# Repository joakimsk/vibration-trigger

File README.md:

# Vibration activated trigger / LED

We use a Piezoelectric element with an operational amplifier (low power amplifier, LM386) to detect small movements. Sensitivity is controlled with potentiometer RV1.

A monostable 555-timer gets triggered, and can be continuously reset, to maintain stable output signal.

The output signal is in this case, driving a LED, but could be used to activate external devices, for example, the purpose of which this was made, an off-the-shelf GPS tracker.

Power supply should probably be 5v regulated... So consider using LM7805 or alternatives. I think a USB power supply connected to a 12v unregulated lead battery should be ok, 5-5.4 volts.

Schematic as PDF available [here](./renders/full_circuit.pdf)

Circuit consists of three components, which I try to explain here.

Latest revision 1.0.0 (first complete prototype).

## Mounting and physical information
Top plane is VCC (+5v), bottom plane is GND.

Mounting is supposed to be with 2x 3mm screw, 1x 2mm screw, 1x 1mm screw (just to test hole sizes).

Full PCB dimensions should be 43.18mm x 40.64mm.

The piezoelectric element needs to be well secured to the vibrating thing, be it your boat engine, your plane or your car. It can very well be a piezoelectric speaker.

## Component: Trigger
The high voltage generated when a piezoelectric crystal is exposed to mechanical load, is compared using LM386 low power amplifier (Voltage Comparator configuration), to an adjustable reference voltage up to VCC (+5v).

I think I ended up with using the LM386 because it had more gain than a standard operational amplifier, but I cannot remember fully. The breadboard edition was tested a year ago.

## Component: Monostable 555
The trigger signal from last component is used to reset a monostable 555 timer. It should toggle output high and take roughly 30 seconds due to size of R6 and C2 before output is low. It is resettable, by activating Q2, which drains C2 when triggered. This means the output signal will be stable, and can be kept high under prolonged vibrations.

## Component: Load
The load is a placeholder for your important equipment. In this example, Q3 turns on LED D1 when input signal is high. Feel free to replace this component with whatever you want to turn on. This is supposed to turn on power to an off-the-shelf GPS tracker.

## BOM
See [xlsx](./BOM.xlsx) for an attempt at BOM.

## Reason
I wanted to track small boats without electric system, using battery power. The vibration from the outboard engine would activate the off-the-shelf GPS tracker, and keep it running while the boat is moving, but turn off when it is standing still. There is a bit of power consumption when disabled, but much less than keeping the GPS running all the time.

## Future work
- Make this all with SMD components.
- Do a better job on the routing.
- Find/make a nice casing.
- Find better connectors.
- Choose more suitable components (trimpot, low power components, 3.3v etc).
- Maybe do some calculations on power consumption.
- Consider making the software for tracking, as well.

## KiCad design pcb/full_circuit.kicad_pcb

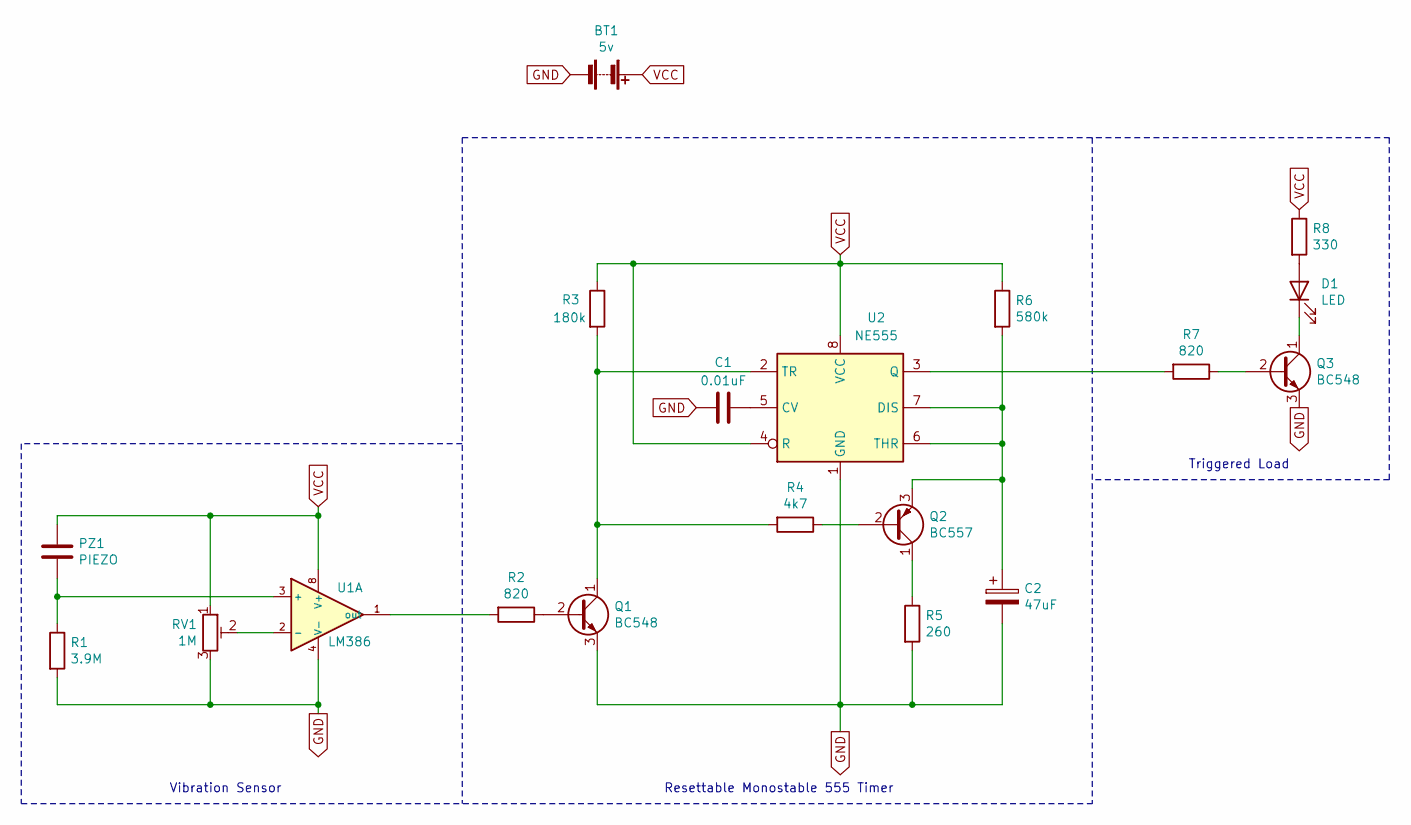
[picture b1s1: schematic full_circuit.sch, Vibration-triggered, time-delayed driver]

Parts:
BT1: 5v; PinSocket_1x02_P2.54mm_Vertical
C1: 0.01uF; CP_Radial_D5.0mm_P2.50mm
C2: 47uF; CP_Radial_D5.0mm_P2.50mm
D1: LED; LED_D5.0mm
PZ1: PIEZO; PinSocket_1x02_P2.54mm_Vertical
Q1, Q3: BC548; TO-92_Inline
Q2: BC557; TO-92_Inline
R1: 3.9M; R_Axial_DIN0204_L3.6mm_D1.6mm_P1.90mm_Vertical
R2, R7: 820; R_Axial_DIN0204_L3.6mm_D1.6mm_P1.90mm_Vertical
R3: 180k; R_Axial_DIN0204_L3.6mm_D1.6mm_P1.90mm_Vertical
R4: 4k7; R_Axial_DIN0204_L3.6mm_D1.6mm_P1.90mm_Vertical
R5: 260; R_Axial_DIN0204_L3.6mm_D1.6mm_P1.90mm_Vertical
R6: 580k; R_Axial_DIN0204_L3.6mm_D1.6mm_P1.90mm_Vertical
R8: 330; R_Axial_DIN0204_L3.6mm_D1.6mm_P1.90mm_Vertical
RV1: 1M; Potentiometer_ACP_CA6-H2,5_Horizontal
U1: LM386; MSOP-8-1EP_3x3mm_P0.65mm_EP1.68x1.88mm
U2: NE555; DIP-8_W7.62mm

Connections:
GND: BT1.2 (-), C1.2, C2.2, Q1.3 (E), Q3.3 (E), R1.2, R5.2, RV1.3, U1.4 (V-), U2.1 (GND)
unnamed: C1.1, U2.5 (CV)
unnamed: C2.1, Q2.3 (E), R6.2, U2.6 (THR), U2.7 (DIS)
unnamed: D1.1 (K), Q3.1 (C)
unnamed: D1.2 (A), R8.2
unnamed: PZ1.2, R1.1, U1.3 (+)
unnamed: Q1.1 (C), R3.2, R4.2, U2.2 (TR)
unnamed: Q1.2 (B), R2.1
unnamed: Q2.1 (C), R5.1
unnamed: Q2.2 (B), R4.1
unnamed: Q3.2 (B), R7.1
unnamed: R2.2, U1.1 (out)
unnamed: R7.2, U2.3 (Q)
unnamed: RV1.2, U1.2 (-)
VCC: BT1.1 (+), PZ1.1, R3.1, R6.1, R8.1, RV1.1, U1.8 (V+), U2.4 (R), U2.8 (VCC)

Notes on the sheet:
Vibration Sensor
Resettable Monostable 555 Timer
Triggered Load

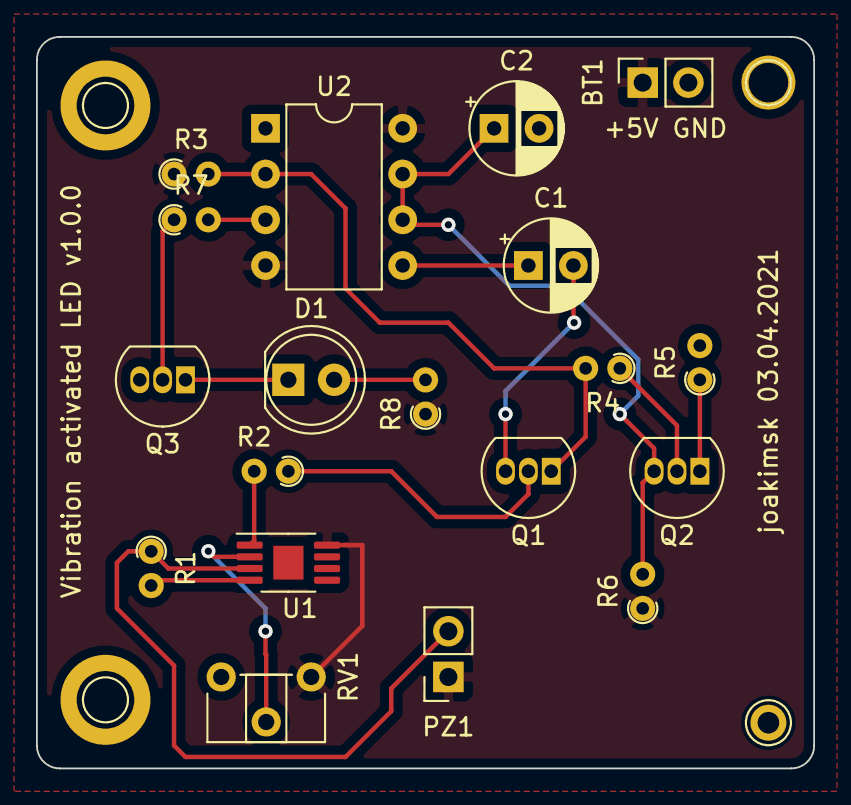
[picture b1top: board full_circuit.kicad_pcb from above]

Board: 2 copper layers, 43.2 x 40.6 mm, 19 parts (0 on the bottom side), 15 nets.

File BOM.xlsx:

Id | Designator | Package | Quantity | Designation | Description
1 | U2 | DIP-8_W7.62mm | 1 | NE555 | 555 timer
2 | R4 | R_Axial_DIN0204_L3.6mm_D1.6mm_P1.90mm_Vertical | 1 | 4k7
3 | R5 | R_Axial_DIN0204_L3.6mm_D1.6mm_P1.90mm_Vertical | 1 | 260
4 | Q1,Q3 | TO-92_Inline | 2 | BC548 | NPN Transistor
6 | Q2 | TO-92_Inline | 1 | BC557 | PNP Transistor
7 | R1 | R_Axial_DIN0204_L3.6mm_D1.6mm_P1.90mm_Vertical | 1 | 3.9M
8 | R2,R7 | R_Axial_DIN0204_L3.6mm_D1.6mm_P1.90mm_Vertical | 2 | 820
9 | R3 | R_Axial_DIN0204_L3.6mm_D1.6mm_P1.90mm_Vertical | 1 | 180k
10 | R6 | R_Axial_DIN0204_L3.6mm_D1.6mm_P1.90mm_Vertical | 1 | 580k
11 | R8 | R_Axial_DIN0204_L3.6mm_D1.6mm_P1.90mm_Vertical | 1 | 330
12 | RV1 | Potentiometer_ACP_CA6-H2,5_Horizontal | 1 | 1M | Potentiometer to adjust trigger sensitivity, should maybe be a trimpot
13 | U1 | MSOP-8-1EP_3x3mm_P0.65mm_EP1.68x1.88mm | 1 | LM386 | Low voltage power amplifier
14 | BT1 | PinSocket_1x02_P2.54mm_Vertical | 1 | 5v
15 | PZ1 | PinSocket_1x02_P2.54mm_Vertical | 1 | PIEZO
16 | C1 | CP_Radial_D5.0mm_P2.50mm | 1 | 0.01uF
17 | C2 | CP_Radial_D5.0mm_P2.50mm | 1 | 47uF
18 | D1 | LED_D5.0mm | 1 | LED

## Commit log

2021-04-03 Small edit to readme
2021-04-03 Added BOM and looked at dimensions
2021-04-03 Gerber files for production
